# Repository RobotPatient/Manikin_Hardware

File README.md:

# Manikin_Hardware
This repo contains the current hardware for the SensorHubs and mainboard of the manikin (BLS - Basic Life Support)

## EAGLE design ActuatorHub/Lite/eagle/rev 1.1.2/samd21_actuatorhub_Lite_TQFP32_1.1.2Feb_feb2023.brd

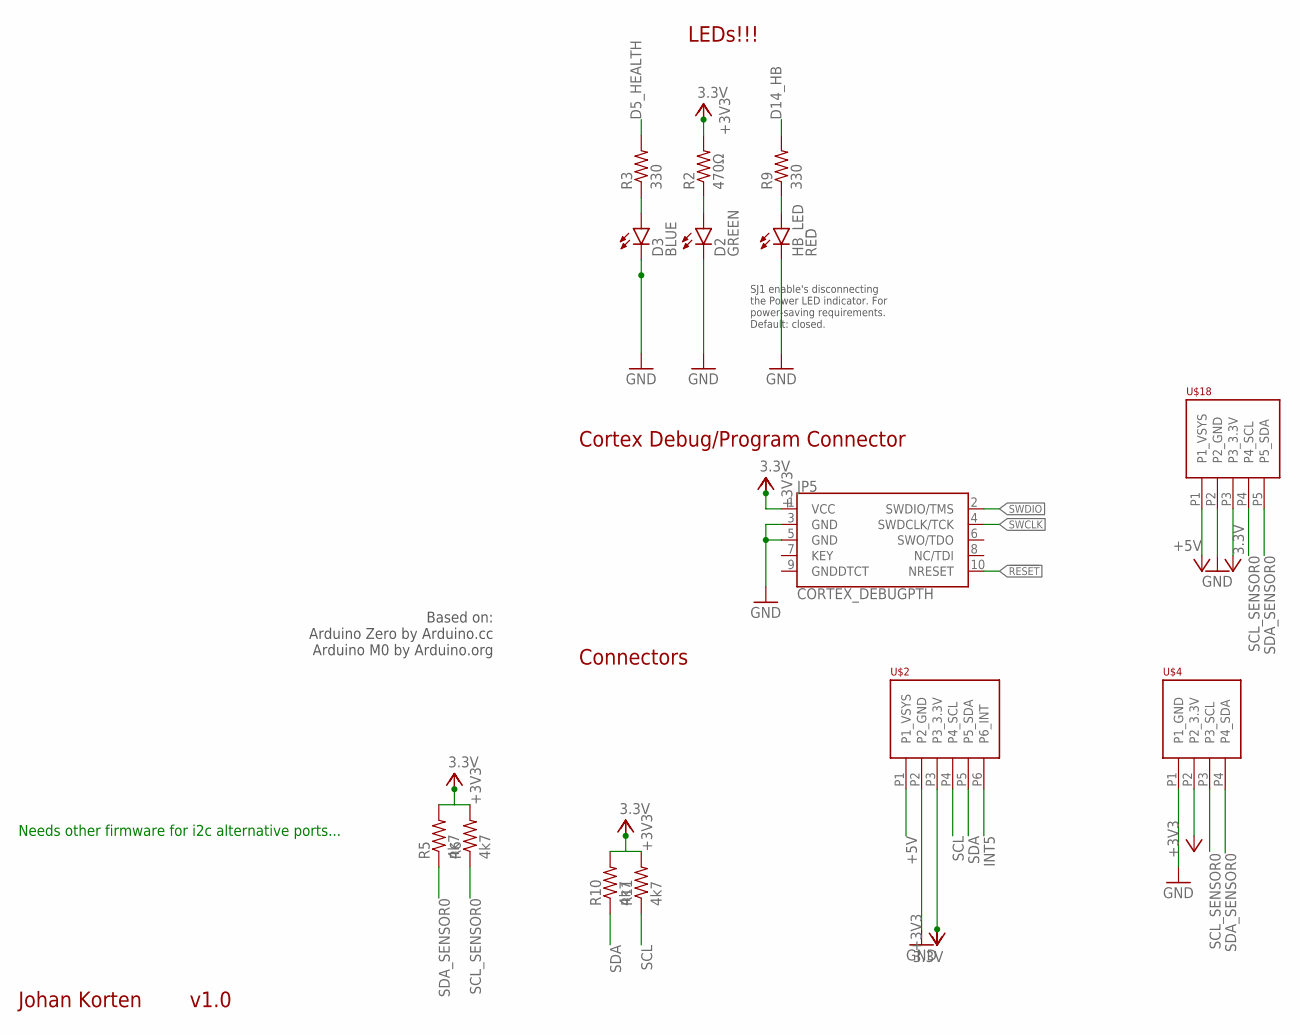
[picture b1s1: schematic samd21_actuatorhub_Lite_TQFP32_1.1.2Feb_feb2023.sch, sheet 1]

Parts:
D2: GREEN; LED-0603
D3: BLUE; LED-0603
HB_LED: RED; LED-0603
JP5: CORTEX_DEBUGPTH; 2X5-PTH-1.27MM
R2: 470Ω; 0603-RES
R3, R9: 330; 0603-RES
R5, R6, R10, R11: 4k7; 0603-RES
U$2: PHOENIX_PTSM_M6_TH_I2CPPANGLE; PTSM_M6_THRHOLE
U$4: PHOENIX_PTSM_M4_THANGLE; PTSM_M4_TH
U$18: PHOENIX_PTSM_M5_TH_I2C++; PTSM_M5_THRHOLE

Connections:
3.3V: JP5.1 (VCC), R2.2, R5.2, R6.2, R10.2, R11.2, U$2.P3 (P3_3.3V), U$4.P2 (P2_3.3V), U$18.P3 (P3_3.3V); also elsewhere on the board
!RESET: JP5.10 (NRESET); also elsewhere on the board
+5V: U$2.P1 (P1_VSYS), U$18.P1 (P1_VSYS); also elsewhere on the board
D5_HEALTH: R3.2; also elsewhere on the board
D5_HEALTH_LED: D3.A, R3.1
D14_HB: R9.2; also elsewhere on the board
D14_HB_LED: HB_LED.A, R9.1
GND: D2.C, D3.C, HB_LED.C, JP5.3 (GND), JP5.5 (GND), U$2.P2 (P2_GND), U$4.P1 (P1_GND), U$18.P2 (P2_GND); also elsewhere on the board
INT5: U$2.P6 (P6_INT); also elsewhere on the board
unnamed: D2.A, R2.1
SCL: R11.1, U$2.P4 (P4_SCL); also elsewhere on the board
SCL_SENSOR0: R6.1, U$4.P3 (P3_SCL), U$18.P4 (P4_SCL); also elsewhere on the board
SDA: R10.1, U$2.P5 (P5_SDA); also elsewhere on the board
SDA_SENSOR0: R5.1, U$4.P4 (P4_SDA), U$18.P5 (P5_SDA); also elsewhere on the board
SWCLK: JP5.4 (SWDCLK/TCK); also elsewhere on the board
SWDIO: JP5.2 (SWDIO/TMS); also elsewhere on the board

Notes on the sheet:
LEDs!!!
Cortex Debug/Program Connector
Connectors
Johan Korten
v1.0
SJ1 enable's disconnecting the Power LED indicator. For power-saving requirements. Default: closed.
Based on: Arduino Zero by Arduino.cc Arduino M0 by Arduino.org
Needs other firmware for i2c alternative ports...

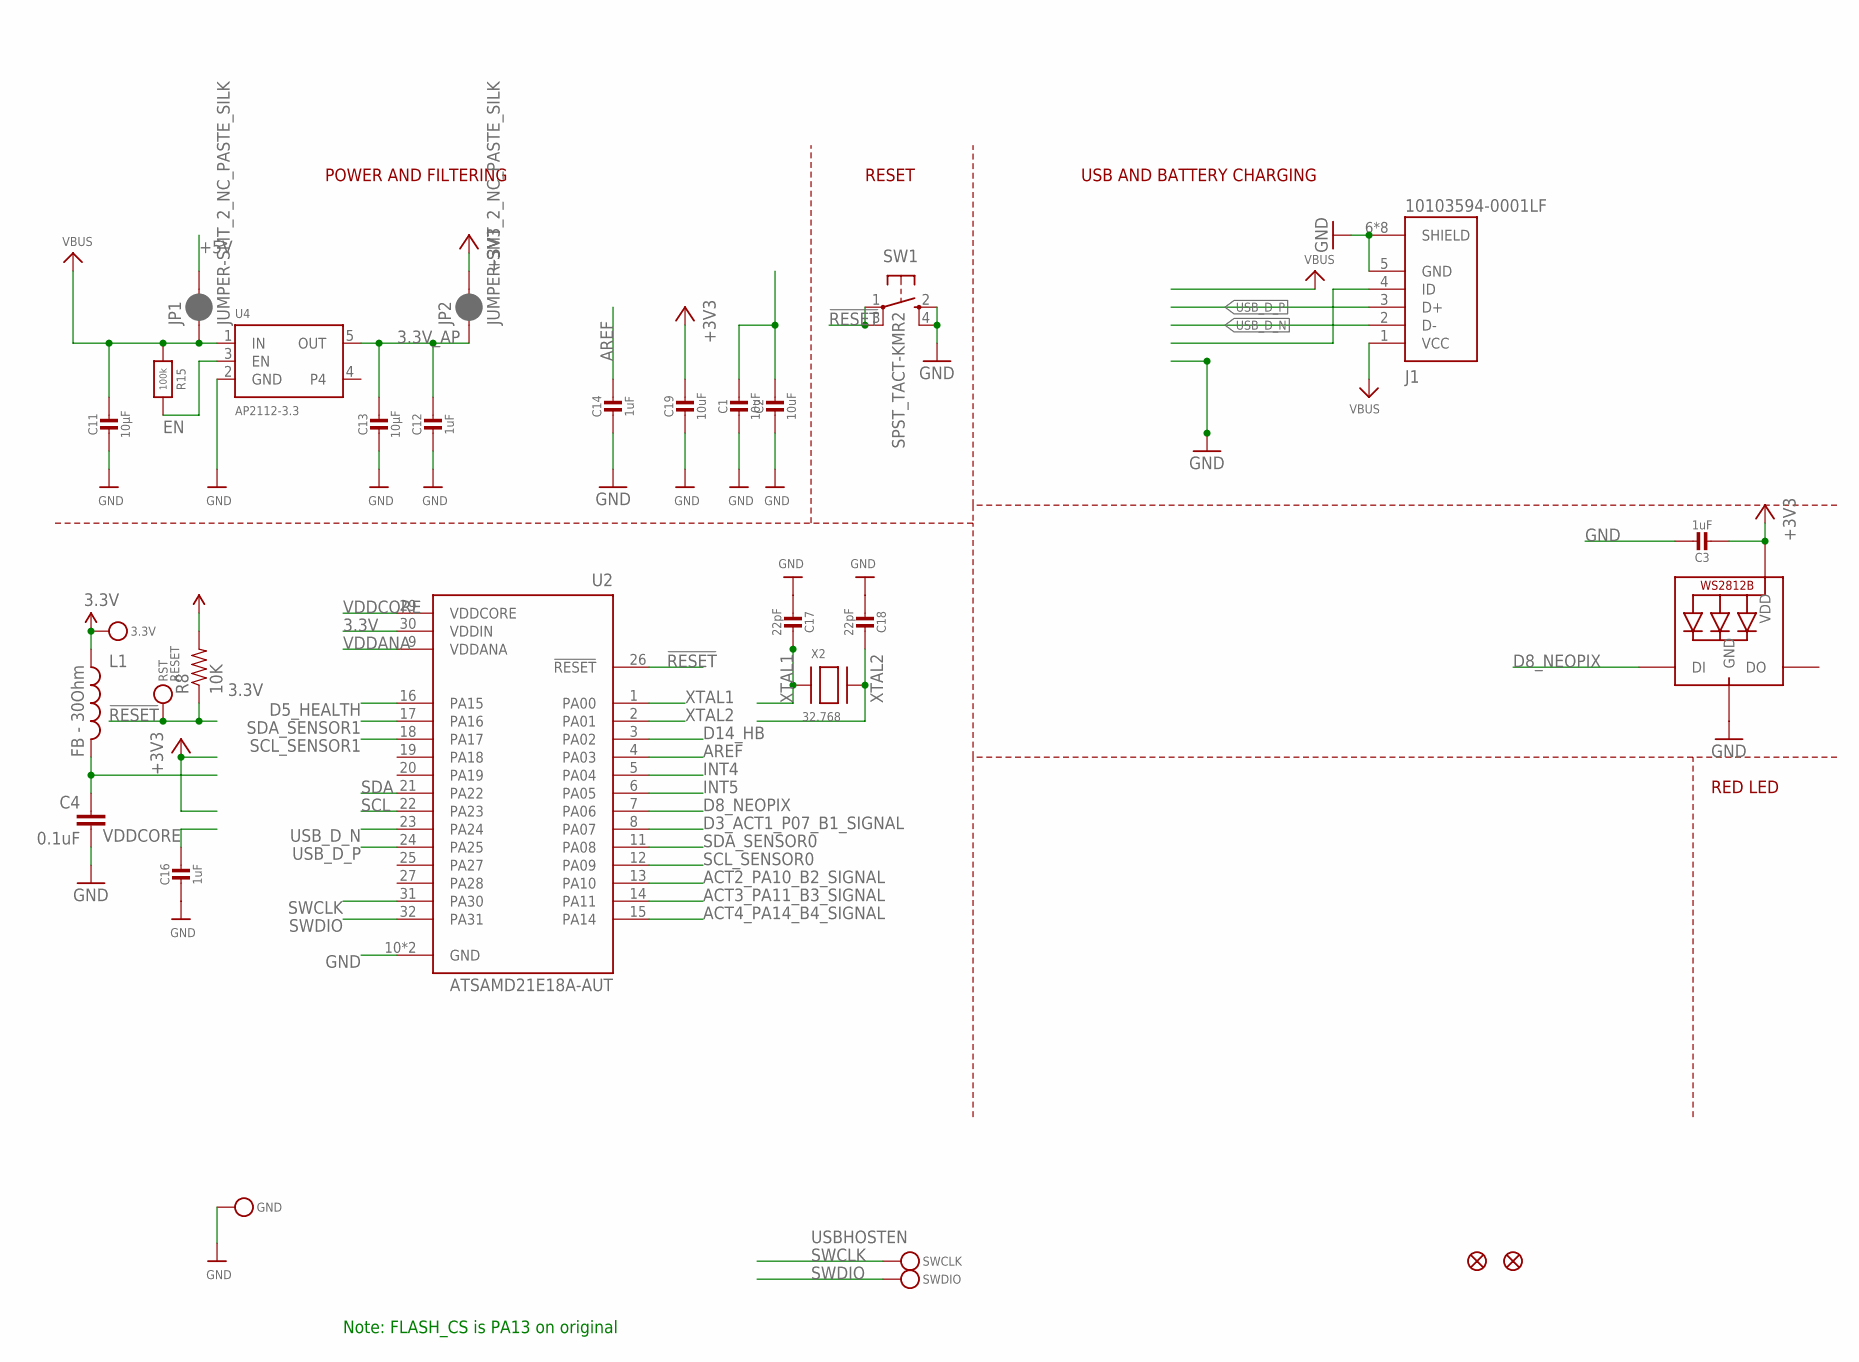
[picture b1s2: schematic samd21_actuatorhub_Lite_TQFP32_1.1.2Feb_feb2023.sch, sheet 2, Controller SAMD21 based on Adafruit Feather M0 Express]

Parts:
3.3V: TESTPOINTROUND1.5MM; TESTPOINT_ROUND_1.5MM
C1, C2, C19: 10uF; 0805-NO
C3, C12, C14, C16: 1uF; 0603-NO
C4: 0.1uF; 0402-CAP
C11, C13: 10µF; 0805-NO
C17, C18: 22pF; 0603-NO
GND: TESTPOINTROUND1.5MM; TESTPOINT_ROUND_1.5MM
J1: 10103594-0001LF; AMPHENOL_10103594-0001LF
JP1, JP2: JUMPER-SMT_2_NC_PASTE_SILK; SMT-JUMPER_2_NC_PASTE_SILK
L1: FB - 30Ohm; 0603
LED1: WS2812B3535; LED3535
R8: 10K; 0603-RES
R15: 100k; 0603-NO
RST: RESET; TESTPOINT_ROUND_1.5MM
SW1: SPST_TACT-KMR2; KMR2
SWCLK: TESTPOINTROUND1.5MM; TESTPOINT_ROUND_1.5MM
SWDIO: TESTPOINTROUND1.5MM; TESTPOINT_ROUND_1.5MM
U2: ATSAMD21E18A-AUT; QFP80P900X900X120-32N
U4: AP2112-3.3; SOT23-5
U$34, U$35: FIDUCIAL""; FIDUCIAL_1MM
X2: 32.768; XTAL3215

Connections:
3.3V: 3.3V.P$1, C3.2, C19.1, JP2.2, L1.1, LED1.2 (VDD), R8.2, U2.30 (VDDIN); also elsewhere on the board
3.3V_AP: C12.1, C13.1, JP2.1, U4.5 (OUT)
!RESET: R8.1, RST.P$1, SW1.1, SW1.3 (P1), U2.26 (!RESET); also elsewhere on the board
+5V: C1.1, C2.1, JP1.2; also elsewhere on the board
ACT2_PA10_B2_SIGNAL: U2.13 (PA10); also elsewhere on the board
ACT3_PA11_B3_SIGNAL: U2.14 (PA11); also elsewhere on the board
ACT4_PA14_B4_SIGNAL: U2.15 (PA14); also elsewhere on the board
AREF: C14.1, U2.4 (PA03)
D3_ACT1_P07_B1_SIGNAL: U2.8 (PA07); also elsewhere on the board
D5_HEALTH: U2.16 (PA15); also elsewhere on the board
D8_NEOPIX: LED1.1 (DI), U2.7 (PA06)
D14_HB: U2.3 (PA02); also elsewhere on the board
EN: R15.2, U4.3 (EN)
GND: C1.2, C2.2, C3.1, C4.2, C11.2, C12.2, C13.2, C14.2, C16.2, C17.2, C18.2, C19.2, GND.P$1, J1.5 (GND), J1.6 (SHIELD), J1.7 (SHIELD), J1.8 (SHIELD), J1.9 (SHIELD), J1.10 (SHIELD), J1.11 (SHIELD), J1.S1 (SHIELD), J1.S2 (SHIELD), LED1.4 (GND), SW1.2 (S), SW1.4 (S1), U2.10 (GND), U2.28 (GND), U4.2 (GND); also elsewhere on the board
INT4: U2.5 (PA04)
INT5: U2.6 (PA05); also elsewhere on the board
SCL: U2.22 (PA23); also elsewhere on the board
SCL_SENSOR0: U2.12 (PA09); also elsewhere on the board
SCL_SENSOR1: U2.18 (PA17)
SDA: U2.21 (PA22); also elsewhere on the board
SDA_SENSOR0: U2.11 (PA08); also elsewhere on the board
SDA_SENSOR1: U2.17 (PA16)
SWCLK: SWCLK.P$1, U2.31 (PA30); also elsewhere on the board
SWDIO: SWDIO.P$1, U2.32 (PA31); also elsewhere on the board
USB_D_N: J1.2 (D-), U2.23 (PA24)
USB_D_P: J1.3 (D+), U2.24 (PA25)
VBUS: C11.1, J1.1 (VCC), JP1.1, R15.1, U4.1 (IN)
VDDANA: C4.1, L1.2, U2.9 (VDDANA)
VDDCORE: C16.1, U2.29 (VDDCORE)
XTAL1: C17.1, U2.1 (PA00), X2.P$1
XTAL2: C18.1, U2.2 (PA01), X2.P$2

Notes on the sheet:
POWER AND FILTERING
RESET
USBHOSTEN
USB AND BATTERY CHARGING
RED LED
Note: FLASH_CS is PA13 on original

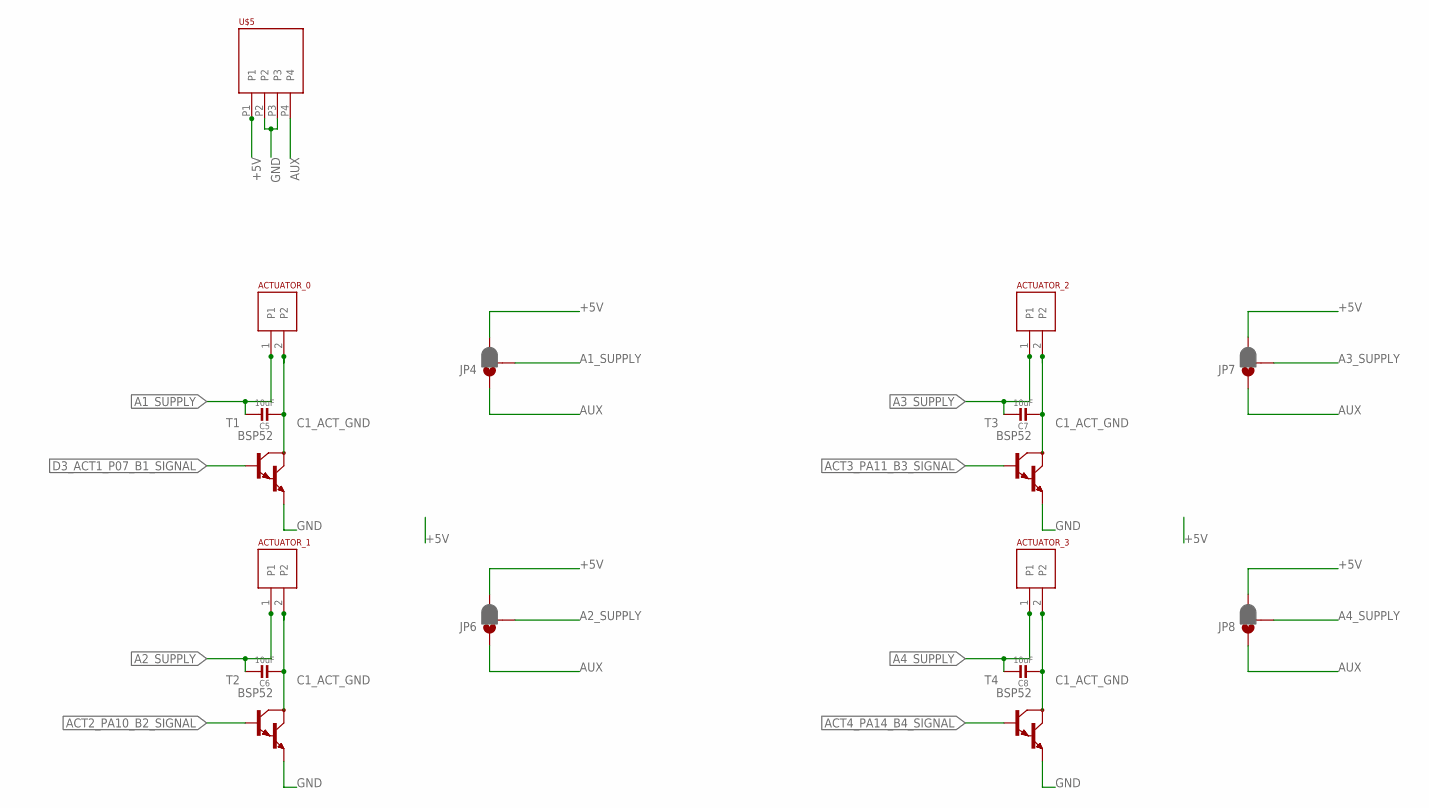
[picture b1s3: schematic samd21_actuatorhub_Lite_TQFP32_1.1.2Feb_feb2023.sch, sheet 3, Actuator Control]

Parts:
ACTUATOR_0, ACTUATOR_1, ACTUATOR_2, ACTUATOR_3: PHOENIX_PTSM_M2TH; PTSM_M2_THRHOLE
C5, C6, C7, C8: 10uF; 0805-NO
JP4, JP6, JP7, JP8: JUMPER-SMT_3_1-NC_PASTE_SILK; SMT-JUMPER_3_1-NC_PASTE_SILK
T1, T2, T3, T4: BSP52; SOT-223-4
U$5: PHOENIX_PTSM_M4_TH_ANGLE; PTSM_M4_TH_ANGLE_NEUTRAL

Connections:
+5V: JP4.3, JP6.3, JP7.3, JP8.3, U$5.P1; also elsewhere on the board
A1_SUPPLY: ACTUATOR_0.1, C5.1, JP4.2
A2_SUPPLY: ACTUATOR_1.1, C6.1, JP6.2
A3_SUPPLY: ACTUATOR_2.1, C7.1, JP7.2
A4_SUPPLY: ACTUATOR_3.1, C8.1, JP8.2
ACT2_PA10_B2_SIGNAL: T2.1 (B); also elsewhere on the board
ACT3_PA11_B3_SIGNAL: T3.1 (B); also elsewhere on the board
ACT4_PA14_B4_SIGNAL: T4.1 (B); also elsewhere on the board
AUX: JP4.1, JP6.1, JP7.1, JP8.1, U$5.P4
C1_ACT_GND: ACTUATOR_0.2, ACTUATOR_1.2, ACTUATOR_2.2, ACTUATOR_3.2, C5.2, C6.2, C7.2, C8.2, T1.2 (C), T1.4 (C), T2.2 (C), T2.4 (C), T3.2 (C), T3.4 (C), T4.2 (C), T4.4 (C)
D3_ACT1_P07_B1_SIGNAL: T1.1 (B); also elsewhere on the board
GND: T1.3 (E), T2.3 (E), T3.3 (E), T4.3 (E), U$5.P2, U$5.P3; also elsewhere on the board

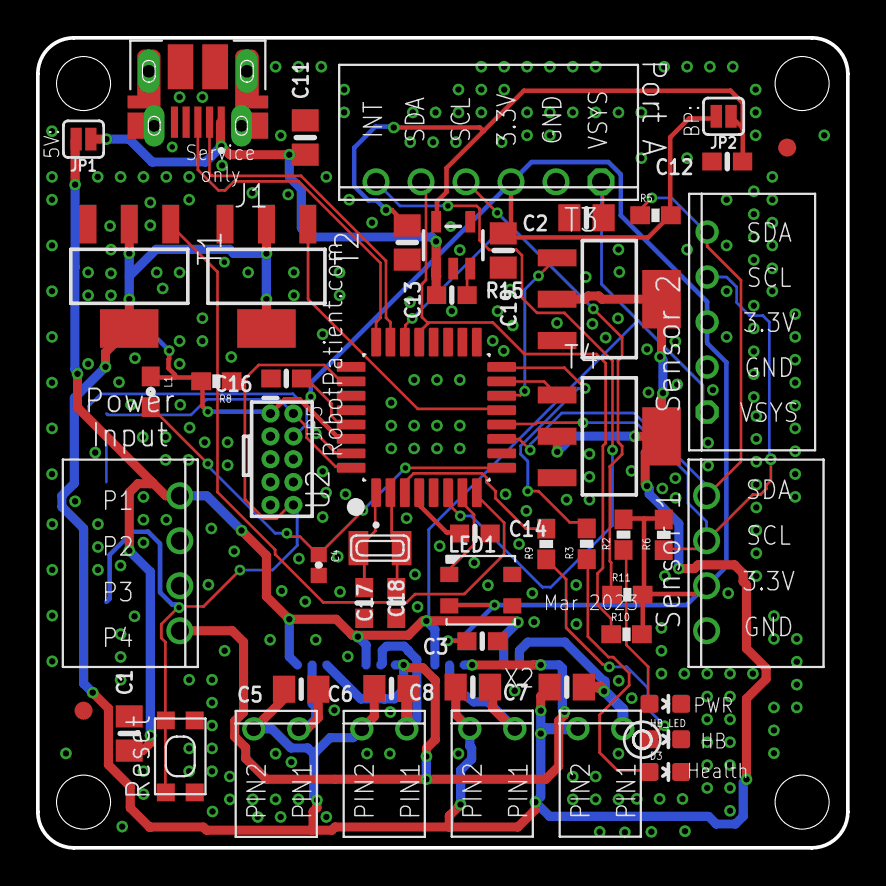
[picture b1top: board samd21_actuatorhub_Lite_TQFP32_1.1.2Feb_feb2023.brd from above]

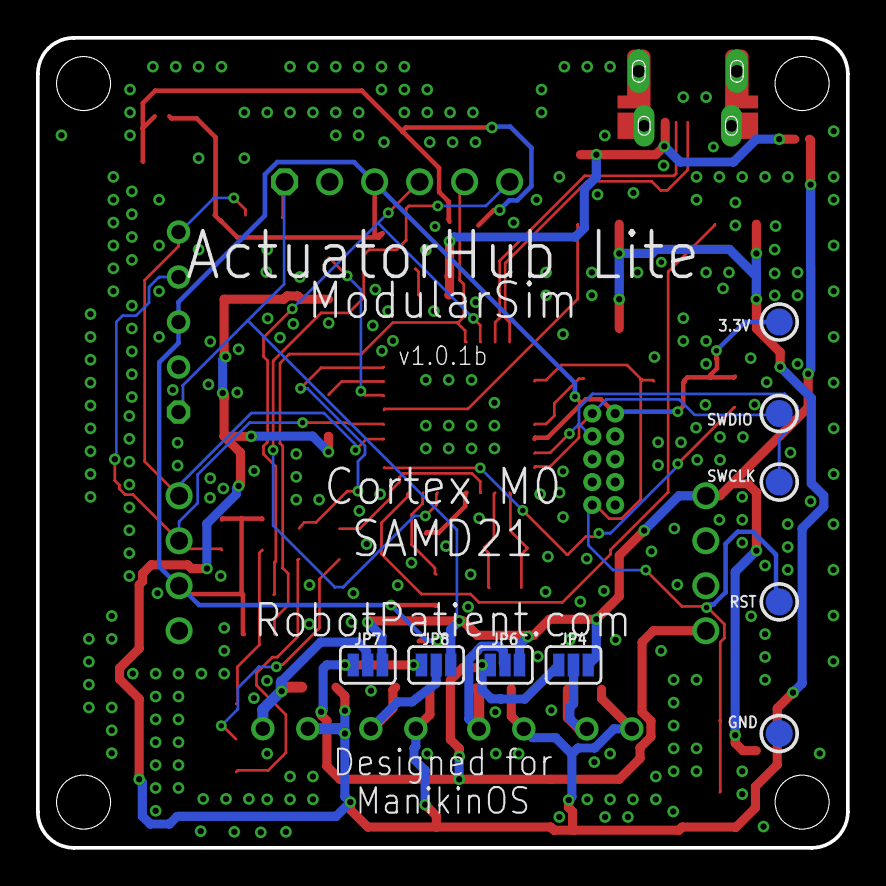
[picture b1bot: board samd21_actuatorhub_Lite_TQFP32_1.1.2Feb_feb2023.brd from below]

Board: 2 copper layers, 45.0 x 45.0 mm, 61 parts (9 on the bottom side), 37 nets.

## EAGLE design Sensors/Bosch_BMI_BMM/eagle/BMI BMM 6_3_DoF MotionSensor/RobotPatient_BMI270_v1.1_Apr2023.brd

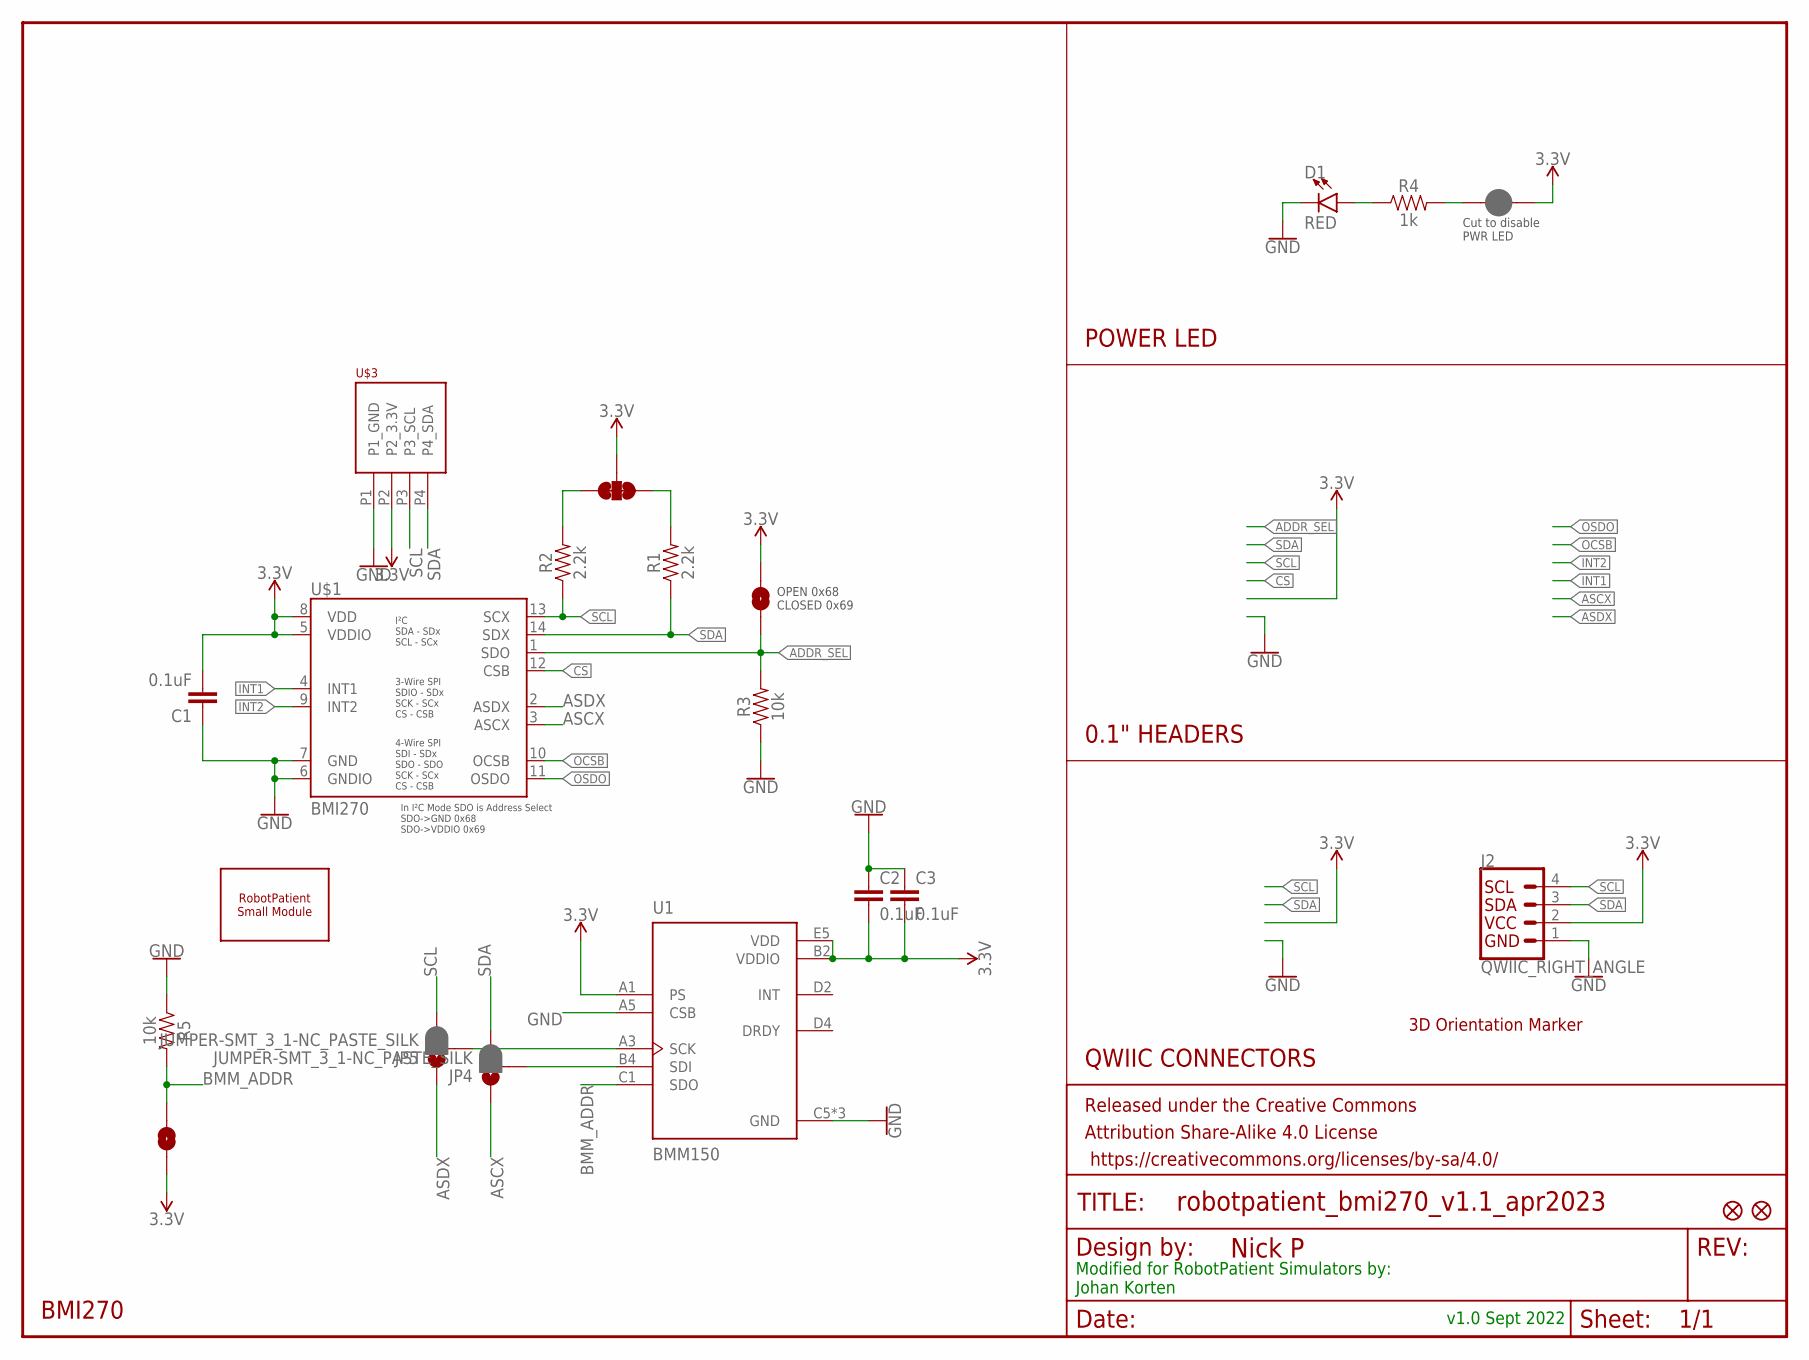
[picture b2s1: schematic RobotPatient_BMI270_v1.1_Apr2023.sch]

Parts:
C1, C2, C3: 0.1uF; 0603
D1: RED; LED-0603
FD1, FD2: FIDUCIAL1X2; FIDUCIAL-1X2
FRAME1: FRAME-LETTERNO_PACKAGE; DUMMY
J2: QWIIC_RIGHT_ANGLE; JST04_1MM_RA
JP1: JUMPER-SMT_3_2-NC_TRACE_SILK; SMT-JUMPER_3_2-NC_TRACE_SILK
JP2, JP6: JUMPER-SMT_2_NO_SILK; SMT-JUMPER_2_NO_SILK
JP3: JUMPER-SMT_2_NC_PASTE_SILK; SMT-JUMPER_2_NC_PASTE_SILK
JP4, JP5: JUMPER-SMT_3_1-NC_PASTE_SILK; SMT-JUMPER_3_1-NC_PASTE_SILK
R1, R2: 2.2k; 0603
R3, R5: 10k; 0603
R4: 1k; 0603
U1: BMM150; XDCR_BMM150
U$1: BMI270
U$2: 3D_MARKER
U$3: PHOENIX_PTSM_M4_THANGLE; PTSM_M4_TH
U$40: ROBOTPATIENT_SMALL_MODULEBOARD; RP_SMALL_SENSOR_OUTLINE

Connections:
3.3V: C1.2, C2.2, C3.2, J2.2, JP1.2, JP2.2, JP3.2, JP6.2, U1.A1 (PS), U1.B2 (VDDIO), U1.E5 (VDD), U$1.5 (VDDIO), U$1.8 (VDD), U$3.P2 (P2_3.3V)
ADDR_SEL: JP2.1, R3.2, U$1.1 (SDO)
ASCX: JP4.1, U$1.3 (ASCX)
ASDX: JP5.1, U$1.2 (ASDX)
BMM_ADDR: JP6.1, R5.2, U1.C1 (SDO)
CS: U$1.12 (CSB)
GND: C1.1, C2.1, C3.1, D1.C, J2.1, R3.1, R5.1, U1.A5 (CSB), U1.C5 (GND), U1.E1 (GND), U1.E3 (GND), U$1.6 (GNDIO), U$1.7 (GND), U$3.P1 (P1_GND)
INT1: U$1.4 (INT1)
INT2: U$1.9 (INT2)
unnamed: JP1.1, R1.2
unnamed: JP1.3, R2.2
unnamed: JP3.1, R4.2
unnamed: D1.A, R4.1
unnamed: JP4.2, U1.B4 (SDI)
unnamed: JP5.2, U1.A3 (SCK)
OCSB: U$1.10 (OCSB)
OSDO: U$1.11 (OSDO)
SCL: J2.4, JP5.3, R2.1, U$1.13 (SCX), U$3.P3 (P3_SCL)
SDA: J2.3, JP4.3, R1.1, U$1.14 (SDX), U$3.P4 (P4_SDA)

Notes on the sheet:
OPEN 0x68 CLOSED 0x69
BMI270
Cut to disable PWR LED
POWER LED
0.1" HEADERS
QWIIC CONNECTORS
Modified for RobotPatient Simulators by: Johan Korten

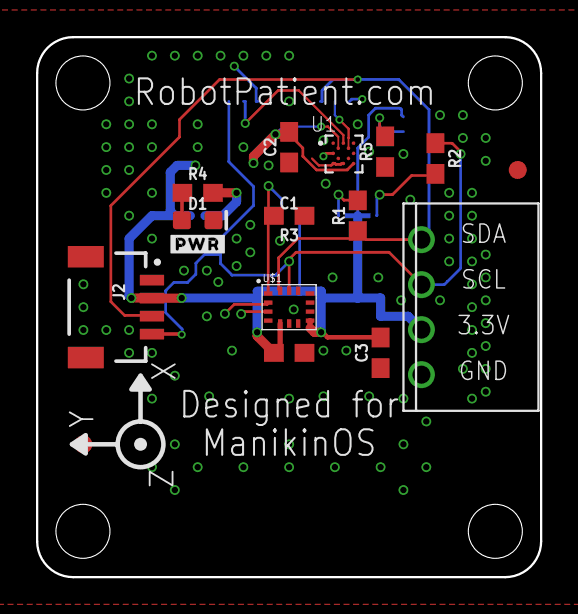
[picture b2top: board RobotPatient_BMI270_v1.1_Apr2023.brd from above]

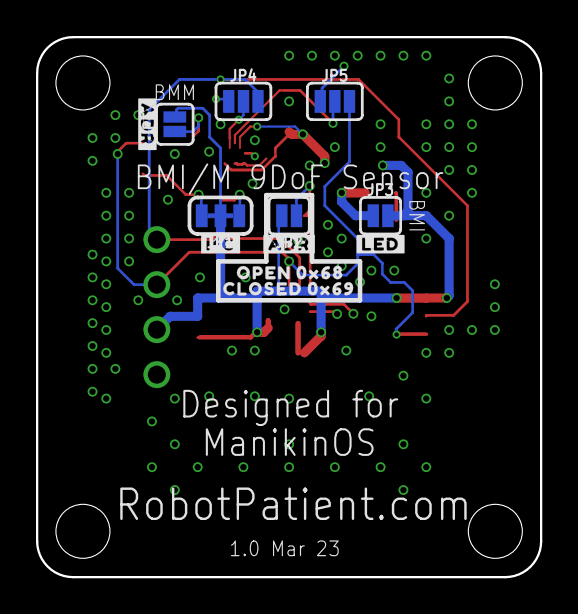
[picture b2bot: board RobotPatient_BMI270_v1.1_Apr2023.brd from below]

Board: 4 copper layers, 28.0 x 30.0 mm, 31 parts (12 on the bottom side), 14 nets.

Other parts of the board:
U$4, U$23: #ADR#2713
U$18: #PWR#2711
U$21: #I�C#2714
U$22: #LED#2712
U$24: OPEN_0X682714
U$25: CLOSED_0X692714

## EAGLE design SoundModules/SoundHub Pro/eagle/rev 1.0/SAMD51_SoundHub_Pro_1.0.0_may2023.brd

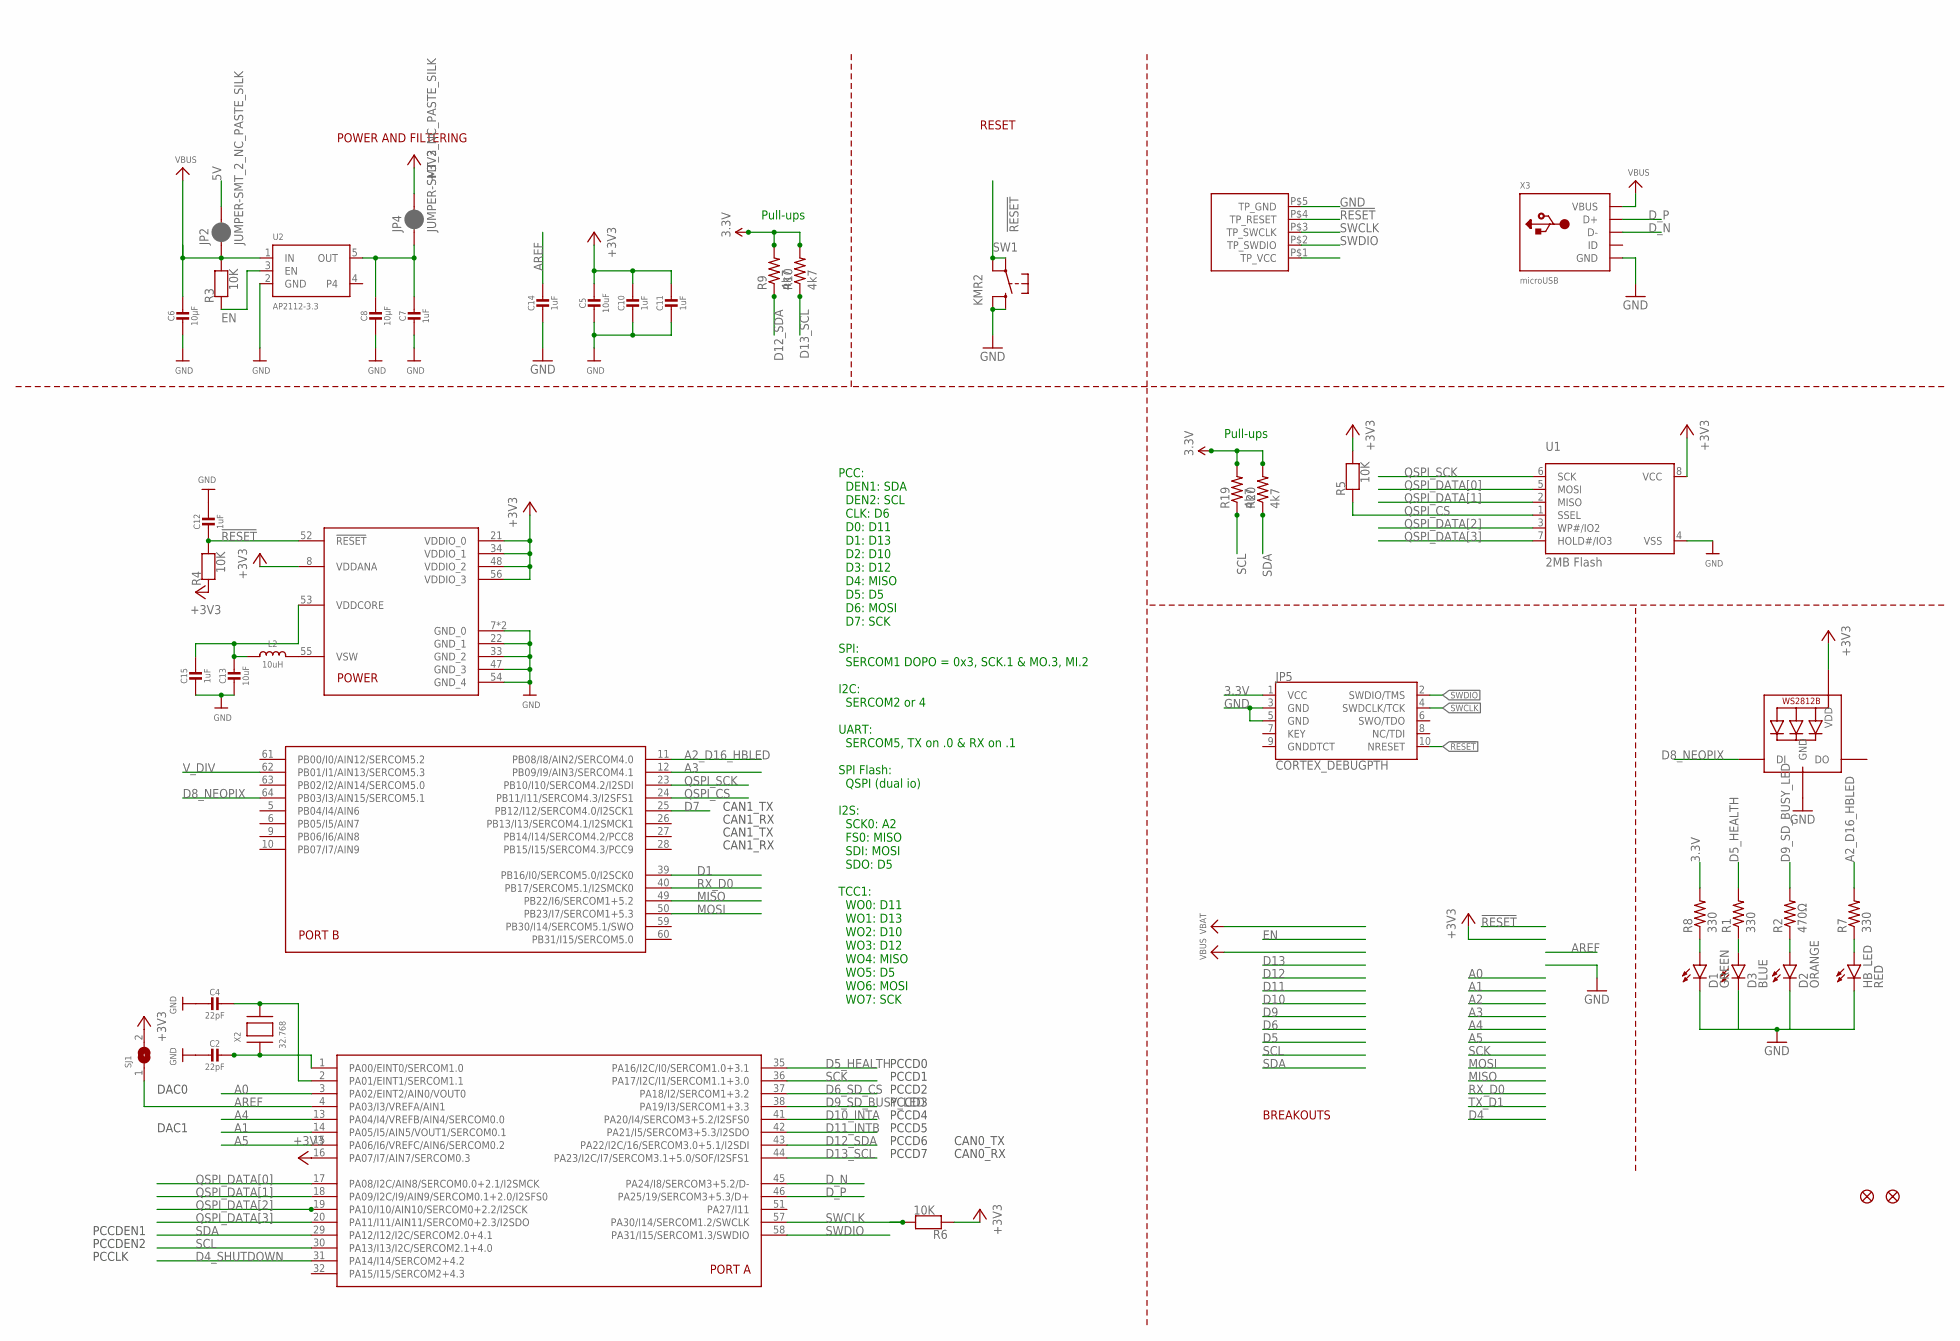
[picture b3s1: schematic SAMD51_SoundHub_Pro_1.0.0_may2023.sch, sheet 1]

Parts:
C2, C4: 22pF; 0603-NO
C5, C13: 10uF; 0805-NO
C6, C8: 10µF; 0805-NO
C7, C10, C11, C12, C14, C15: 1uF; 0603-NO
D1: GREEN; LED-0603@1
D2: ORANGE; LED-0603
D3: BLUE; LED-0603@1
HB_LED: RED; LED-0603
JP2, JP4: JUMPER-SMT_2_NC_PASTE_SILK; SMT-JUMPER_2_NC_PASTE_SILK
JP5: CORTEX_DEBUGPTH; 2X5-PTH-1.27MM
L2: 10uH; INDUCTOR_1007
LED1: WS2812B3535; LED3535
R1, R7, R8: 330; 0603-RES
R2: 470Ω; 0603-RES
R3, R4, R5, R6: 10K; 0603-NO
R9, R10, R19, R20: 4k7; 0603-RES
SJ1: SOLDERJUMPERCLOSED; SOLDERJUMPER_CLOSEDWIRE
SW1: KMR2; BTN_KMR2_4.6X2.8
U1: 2MB Flash; USON8
U2: AP2112-3.3; SOT23-5
U$12: HUB_TESTPINSHUBS; TEST_PINS
U$14: ATSAMD51J; PQFN64-1
U$34, U$35: FIDUCIAL_1MM
X2: 32.768; XTAL3215
X3: microUSB; 4UCONN_20329_V2

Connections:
3.3V: C5.1, C10.1, C11.1, JP4.2, JP5.1 (VCC), LED1.2 (VDD), R4.1, R5.2, R6.1, R8.2, R9.2, R10.2, R19.2, R20.2, SJ1.2, U1.8 (VCC), U$12.P$1 (TP_VCC), U$14.8 (VDDANA), U$14.16 (PA07/I7/AIN7/SERCOM0.3), U$14.21 (VDDIO_0), U$14.34 (VDDIO_1), U$14.48 (VDDIO_2), U$14.56 (VDDIO_3); also elsewhere on the board
5V: JP2.2; also elsewhere on the board
!RESET: C12.2, JP5.10 (NRESET), R4.2, SW1.A, SW1.A' (P1), U$12.P$4 (TP_RESET), U$14.52 (!RESET)
A0: U$14.3 (PA02/EINT2/AIN0/VOUT0); also elsewhere on the board
A1: U$14.14 (PA05/I5/AIN5/VOUT1/SERCOM0.1); also elsewhere on the board
A2_D16_HBLED: R7.2, U$14.11 (PB08/I8/AIN2/SERCOM4.0)
A3: U$14.12 (PB09/I9/AIN3/SERCOM4.1)
A4: U$14.13 (PA04/I4/VREFB/AIN4/SERCOM0.0)
A5: U$14.15 (PA06/I6/VREFC/AIN6/SERCOM0.2)
AREF: C14.1, SJ1.1, U$14.4 (PA03/I3/VREFA/AIN1)
D1: U$14.39 (PB16/I0/SERCOM5.0/I2SCK0)
D4_SHUTDOWN: U$14.31 (PA14/I14/SERCOM2+4.2); also elsewhere on the board
D5_HEALTH: R1.2, U$14.35 (PA16/I2C/I0/SERCOM1.0+3.1)
D5_HEALTH_LED: D3.A, R1.1
D5_HEALTH_LED1: D1.A, R8.1
D6_SD_CS: U$14.37 (PA18/I2/SERCOM1+3.2); also elsewhere on the board
D7: U$14.25 (PB12/I12/SERCOM4.0/I2SCK1); also elsewhere on the board
D8_NEOPIX: LED1.1 (DI), U$14.64 (PB03/I3/AIN15/SERCOM5.1)
D9_SD_BUSY_LED: R2.2, U$14.38 (PA19/I3/SERCOM1+3.3)
D10_INTA: U$14.41 (PA20/I4/SERCOM3+5.2/I2SFS0); also elsewhere on the board
D11_INTB: U$14.42 (PA21/I5/SERCOM3+5.3/I2SDO); also elsewhere on the board
D12_SDA: R9.1, U$14.43 (PA22/I2C/16/SERCOM3.0+5.1/I2SDI); also elsewhere on the board
D13_SCL: R10.1, U$14.44 (PA23/I2C/I7/SERCOM3.1+5.0/SOF/I2SFS1); also elsewhere on the board
D14_HB_LED: HB_LED.A, R7.1
D_N: U$14.45 (PA24/I8/SERCOM3+5.2/D-), X3.D-
D_P: U$14.46 (PA25/19/SERCOM3+5.3/D+), X3.D+
EN: R3.1, U2.3 (EN)
GND: C2.2, C4.2, C5.2, C6.2, C7.2, C8.2, C10.2, C11.2, C12.1, C13.2, C14.2, C15.2, D1.C, HB_LED.C, JP5.3 (GND), JP5.5 (GND), LED1.4 (GND), SW1.B (S), SW1.B' (S1), U1.4 (VSS), U2.2 (GND), U$12.P$5 (TP_GND), U$14.7 (GND_0), U$14.22 (GND_1), U$14.33 (GND_2), U$14.47 (GND_3), U$14.54 (GND_4), U$14.EXP (GND_0), X3.BASE@1 (GND), X3.BASE@2 (GND), X3.GND, X3.SPRT@1 (GND), X3.SPRT@2 (GND), X3.SPRT@3 (GND), X3.SPRT@4 (GND); also elsewhere on the board
MISO: U$14.49 (PB22/I6/SERCOM1+5.2); also elsewhere on the board
MOSI: U$14.50 (PB23/I7/SERCOM1+5.3); also elsewhere on the board
unnamed: D2.A, R2.1
unnamed: C2.1, U$14.1 (PA00/EINT0/SERCOM1.0), X2.P$1
unnamed: C4.1, U$14.2 (PA01/EINT1/SERCOM1.1), X2.P$2
unnamed: L2.P$2 (2), U$14.55 (VSW)
OUT: C7.1, C8.1, JP4.1, U2.5 (OUT)
QSPI_CS: R5.1, U1.1 (SSEL), U$14.24 (PB11/I11/SERCOM4.3/I2SFS1)
QSPI_DATA[0]: U1.5 (MOSI), U$14.17 (PA08/I2C/AIN8/SERCOM0.0+2.1/I2SMCK)
QSPI_DATA[1]: U1.2 (MISO), U$14.18 (PA09/I2C/I9/AIN9/SERCOM0.1+2.0/I2SFS0)
QSPI_DATA[2]: U1.3 (WP#/IO2), U$14.19 (PA10/I10/AIN10/SERCOM0+2.2/I2SCK)
QSPI_DATA[3]: U1.7 (HOLD#/IO3), U$14.20 (PA11/I11/AIN11/SERCOM0+2.3/I2SDO)
QSPI_SCK: U1.6 (SCK), U$14.23 (PB10/I10/SERCOM4.2/I2SDI)
RX_D0: U$14.40 (PB17/SERCOM5.1/I2SMCK0)
SCK: U$14.36 (PA17/I2C/I1/SERCOM1.1+3.0); also elsewhere on the board
SCL: R19.1, U$14.30 (PA13/I13/I2C/SERCOM2.1+4.0); also elsewhere on the board
SDA: R20.1, U$14.29 (PA12/I12/I2C/SERCOM2.0+4.1); also elsewhere on the board
SWCLK: JP5.4 (SWDCLK/TCK), R6.2, U$12.P$3 (TP_SWCLK), U$14.57 (PA30/I14/SERCOM1.2/SWCLK)
SWDIO: JP5.2 (SWDIO/TMS), U$12.P$2 (TP_SWDIO), U$14.58 (PA31/I15/SERCOM1.3/SWDIO)
VBUS: C6.1, JP2.1, R3.2, U2.1 (IN), X3.VBUS
VDDCORE1: C13.1, C15.1, L2.P$1 (1), U$14.53 (VDDCORE)
V_DIV: U$14.62 (PB01/I1/AIN13/SERCOM5.3)

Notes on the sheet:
POWER AND FILTERING
RESET
BREAKOUTS
PCCDEN1
PCCDEN2
PCCD0
PCCD1
PCCD2
PCCD3
PCCD4
PCCD5
PCCD6
PCCD7
PCCLK
PCC: DEN1: SDA DEN2: SCL CLK: D6 D0: D11 D1: D13 D2: D10 D3: D12 D4: MISO D5: D5 D6: MOSI D7: SCK SPI: SERCOM1 DOPO = 0x3, SCK.1 & MO.3, MI.2 I2C: SERCOM2 or 4 UART: SERCOM5, TX on .0 & RX on .1 SPI Flash: QSPI (dual io) I2S: SCK0: A2 FS0: MISO SDI: MOSI SDO: D5 TCC1: WO0: D11 WO1: D13 WO2: D10 WO3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
CAN0_TX
CAN0_RX
DAC0
DAC1
CAN1_TX
CAN1_RX
Pull-ups

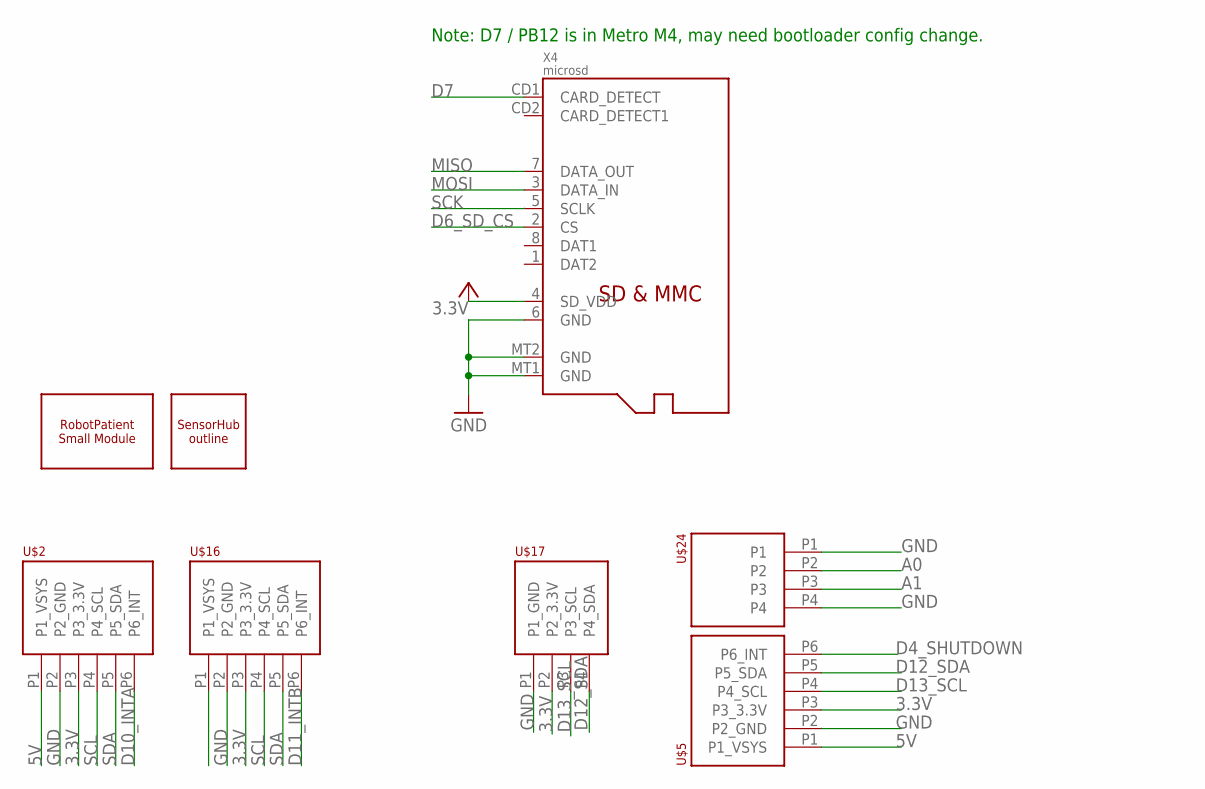
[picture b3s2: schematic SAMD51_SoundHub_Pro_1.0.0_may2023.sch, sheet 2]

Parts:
U$2, U$5, U$16: PHOENIX_PTSM_M6_TH_I2CPPANGLE; PTSM_M6_THRHOLE
U$7: SENSORHUB_PROFILEUSB_LEFT; SENSORHUB_OUTLINE_USB_NOTCH_LEFT
U$9: ROBOTPATIENT_SMALL_MODULEOUTLINE; ROBOTPATIENT_SMALL
U$17: PHOENIX_PTSM_M4_THANGLE; PTSM_M4_TH
U$24: PHOENIX_PTSM_M4_TH_ANGLE; PTSM_M4_TH_ANGLE_NEUTRAL
X4: microsd; MICROSD

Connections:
3.3V: U$2.P3 (P3_3.3V), U$5.P3 (P3_3.3V), U$16.P3 (P3_3.3V), U$17.P2 (P2_3.3V), X4.4 (SD_VDD); also elsewhere on the board
5V: U$2.P1 (P1_VSYS), U$5.P1 (P1_VSYS), U$16.P1 (P1_VSYS); also elsewhere on the board
A0: U$24.P2; also elsewhere on the board
A1: U$24.P3; also elsewhere on the board
D4_SHUTDOWN: U$5.P6 (P6_INT); also elsewhere on the board
D6_SD_CS: X4.2 (CS); also elsewhere on the board
D7: X4.CD1 (CARD_DETECT); also elsewhere on the board
D10_INTA: U$2.P6 (P6_INT); also elsewhere on the board
D11_INTB: U$16.P6 (P6_INT); also elsewhere on the board
D12_SDA: U$5.P5 (P5_SDA), U$17.P4 (P4_SDA); also elsewhere on the board
D13_SCL: U$5.P4 (P4_SCL), U$17.P3 (P3_SCL); also elsewhere on the board
GND: U$2.P2 (P2_GND), U$5.P2 (P2_GND), U$16.P2 (P2_GND), U$17.P1 (P1_GND), U$24.P1, U$24.P4, X4.6 (GND), X4.MT1 (GND), X4.MT2 (GND); also elsewhere on the board
MISO: X4.7 (DATA_OUT); also elsewhere on the board
MOSI: X4.3 (DATA_IN); also elsewhere on the board
SCK: X4.5 (SCLK); also elsewhere on the board
SCL: U$2.P4 (P4_SCL), U$16.P4 (P4_SCL); also elsewhere on the board
SDA: U$2.P5 (P5_SDA), U$16.P5 (P5_SDA); also elsewhere on the board

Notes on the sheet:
Note: D7 / PB12 is in Metro M4, may need bootloader config change.

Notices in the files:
parts and their libraries:
SparkFun-Resistors: Licensing: Creative Commons ShareAlike 4.0 International - https://creativecommons.org/licenses/by-sa/4.0
microbuilder: This work is placed in the public domain, and may be freely used for commercial and non-commercial work with the following conditions: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
